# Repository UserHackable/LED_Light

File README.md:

## 4H-LedLight 

### Board dimensions

* (110000, 115000) original units
* (1.1000, 1.1500) inches
* (27.9400, 29.2100) mm

| Front | Back |
| --- | --- |
|  |  |

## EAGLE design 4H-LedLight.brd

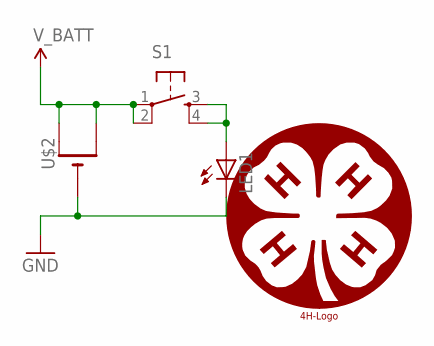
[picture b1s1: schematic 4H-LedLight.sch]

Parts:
LED1: LEDOVAL; LED-OVAL
S1: TAC_SWITCHPTH; TACTILE-PTH
U$1: 4H-LOGO6; 4H_LOGO_6
U$2: CR2032THM; CR2032-THRU

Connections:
GND: LED1.CATHODE (C), U$2.-
unnamed: LED1.ANODE (A), S1.3, S1.4
V_BATT: S1.1, S1.2, U$2.+1 (+), U$2.+2 (+1)

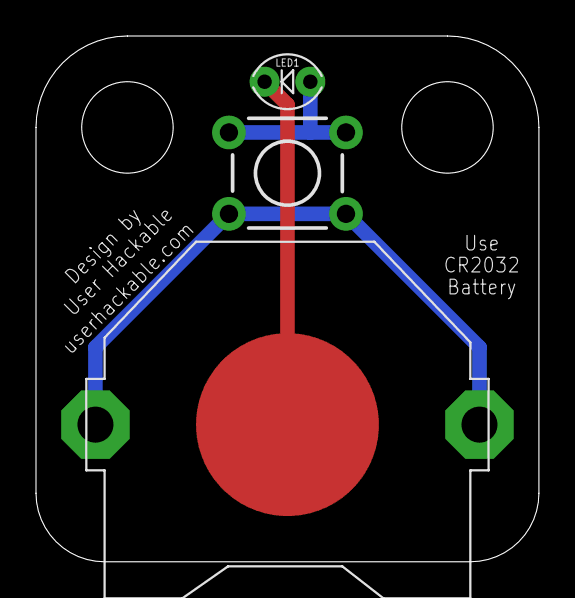
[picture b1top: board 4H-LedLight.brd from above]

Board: 2 copper layers, 27.9 x 29.2 mm, 4 parts (1 on the bottom side), 3 nets.

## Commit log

2016-04-07 from Makefile

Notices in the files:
parts and their libraries:
SparkFun-Aesthetics: Licensing: Creative Commons ShareAlike 4.0 International - https://creativecommons.org/licenses/by-sa/4.0
